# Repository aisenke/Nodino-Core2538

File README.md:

Nodino-Core2538
===============

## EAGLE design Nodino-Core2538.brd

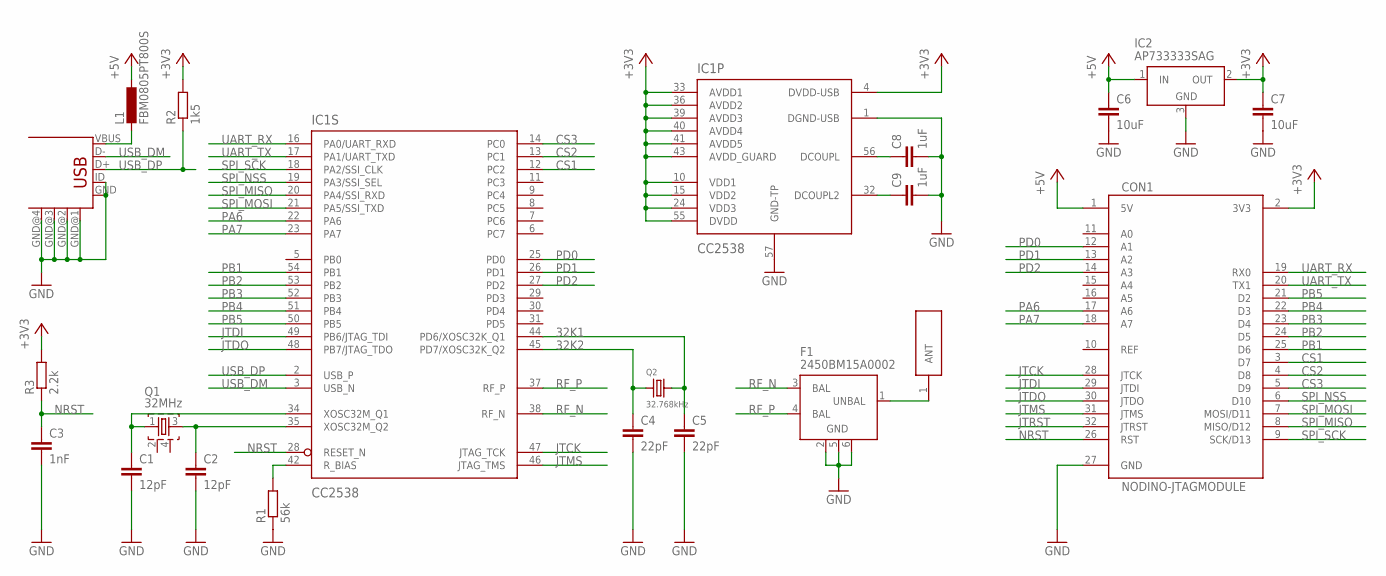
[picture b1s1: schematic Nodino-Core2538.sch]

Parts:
ANT1: 2450AT18B100
C1, C2: 12pF; C0603K
C3: 1nF; C0603K
C4, C5: 22pF; C0603K
C6, C7: 10uF; C0603K
C8, C9: 1uF; C0603K
CON1: NODINO-JTAGMODULE; NODINO-JTAG-MOD
CON2: USB-OTG_SHIELD; USB-UAB-S1
F1: 2450BM15A0002
IC1: CC2538; QFN56P800X800X100-57N
IC2: AP733333SAG; SOT23
L1: FBM0805PT800S; L0805
Q1: 32MHz; FA-20H
Q2: 32.768kHz; ABS07
R1: 56k; R0603K
R2: 1k5; R0603K
R3: 2.2k; R0603K

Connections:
32K1: C5.1, IC1.44 (PD6/XOSC32K_Q1), Q2.2
32K2: C4.1, IC1.45 (PD7/XOSC32K_Q2), Q2.1
+3V3: C7.1, CON1.2 (3V3), IC1.4 (DVDD-USB), IC1.10 (VDD1), IC1.15 (VDD2), IC1.24 (VDD3), IC1.33 (AVDD1), IC1.36 (AVDD2), IC1.39 (AVDD3), IC1.40 (AVDD4), IC1.41 (AVDD5), IC1.43 (AVDD_GUARD), IC1.55 (DVDD), IC2.2 (OUT), R2.2, R3.2
+5V: C6.1, CON1.1 (5V), IC2.1 (IN), L1.1
CS1: CON1.3 (D7), IC1.12 (PC2)
CS2: CON1.4 (D8), IC1.13 (PC1)
CS3: CON1.5 (D9), IC1.14 (PC0)
GND: C1.2, C2.2, C3.2, C4.2, C5.2, C6.2, C7.2, C8.2, C9.2, CON1.27 (GND), CON2.GND, CON2.GND@1 (GND), CON2.GND@2 (GND), CON2.GND@3 (GND), CON2.GND@4 (GND), CON2.ID, F1.2 (GND), F1.5 (GND), F1.6 (GND), IC1.1 (DGND-USB), IC1.57 (GND-TP), IC2.3 (GND), R1.1
JTCK: CON1.28 (JTCK), IC1.47 (JTAG_TCK)
JTDI: CON1.29 (JTDI), IC1.49 (PB6/JTAG_TDI)
JTDO: CON1.30 (JTDO), IC1.48 (PB7/JTAG_TDO)
JTMS: CON1.31 (JTMS), IC1.46 (JTAG_TMS)
JTRST: CON1.32 (JTRST)
unnamed: CON2.VBUS, L1.2
unnamed: ANT1.1, F1.1 (UNBAL)
unnamed: C8.1, IC1.56 (DCOUPL)
unnamed: C9.1, IC1.32 (DCOUPL2)
unnamed: IC1.42 (R_BIAS), R1.2
unnamed: C2.1, IC1.35 (XOSC32M_Q2), Q1.3
unnamed: C1.1, IC1.34 (XOSC32M_Q1), Q1.1
NRST: C3.1, CON1.26 (RST), IC1.28 (RESET_N), R3.1
PA6: CON1.17 (A6), IC1.22 (PA6)
PA7: CON1.18 (A7), IC1.23 (PA7)
PB1: CON1.25 (D6), IC1.54 (PB1)
PB2: CON1.24 (D5), IC1.53 (PB2)
PB3: CON1.23 (D4), IC1.52 (PB3)
PB4: CON1.22 (D3), IC1.51 (PB4)
PB5: CON1.21 (D2), IC1.50 (PB5)
PD0: CON1.12 (A1), IC1.25 (PD0)
PD1: CON1.13 (A2), IC1.26 (PD1)
PD2: CON1.14 (A3), IC1.27 (PD2)
RF_N: F1.3 (BAL), IC1.38 (RF_N)
RF_P: F1.4 (BAL), IC1.37 (RF_P)
SPI_MISO: CON1.8 (MISO/D12), IC1.20 (PA4/SSI_RXD)
SPI_MOSI: CON1.7 (MOSI/D11), IC1.21 (PA5/SSI_TXD)
SPI_NSS: CON1.6 (D10), IC1.19 (PA3/SSI_SEL)
SPI_SCK: CON1.9 (SCK/D13), IC1.18 (PA2/SSI_CLK)
UART_RX: CON1.19 (RX0), IC1.16 (PA0/UART_RXD)
UART_TX: CON1.20 (TX1), IC1.17 (PA1/UART_TXD)
USB_DM: CON2.D-, IC1.3 (USB_N)
USB_DP: CON2.D+, IC1.2 (USB_P), R2.1

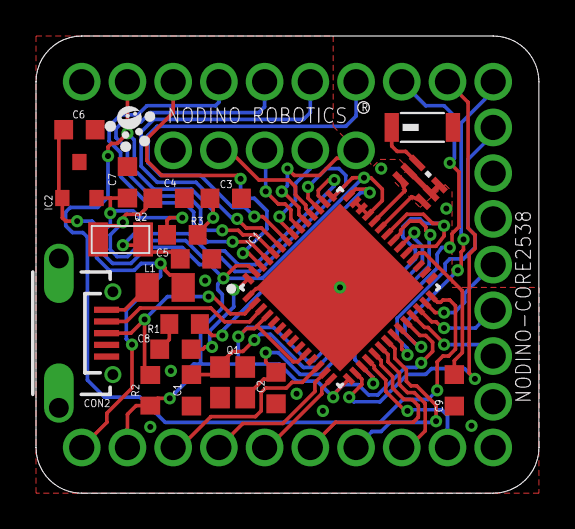
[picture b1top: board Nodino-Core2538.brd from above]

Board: 2 copper layers, 27.9 x 25.4 mm, 21 parts (0 on the bottom side), 40 nets.

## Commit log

2014-04-11 almost done, but I think we need to remove the chip antenna
2014-04-11 all connected, except CC2538 ground pad and balun
2014-04-11 all done! but need to check and double check again before fab
2014-04-12 added CS1, CS2, CS3
2014-04-13 added D2-D6
2014-04-13 update for D2-D6
2014-04-13 final version, but still missing A0-A5 and AREF
2014-04-14 added D15-D17
2014-04-14 name and value alignment
2014-04-24 library update
